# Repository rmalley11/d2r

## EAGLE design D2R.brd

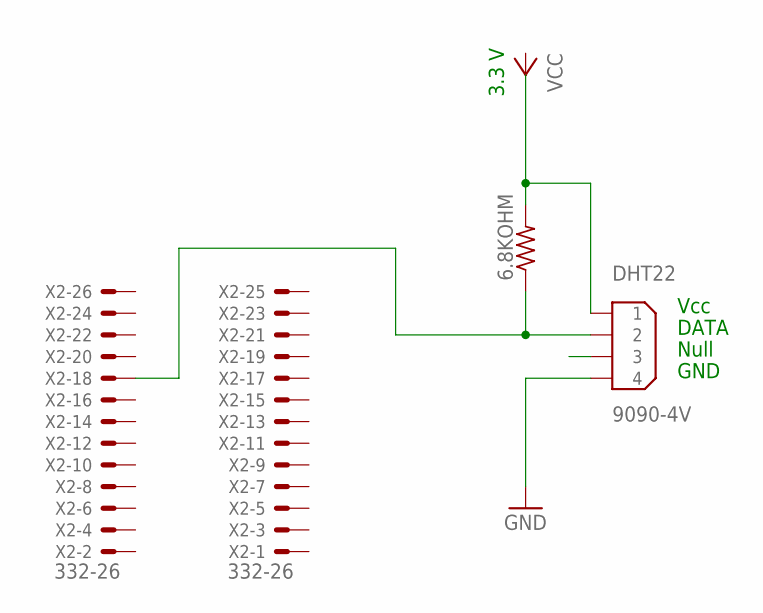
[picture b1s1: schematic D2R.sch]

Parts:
6.8KOHM: R-US_0207/10; 0207/10
DHT22: 9090-4V
X2: 332-26

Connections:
GND: DHT22.4
unnamed: 6.8KOHM.2, DHT22.1
unnamed: 6.8KOHM.1, DHT22.2, X2.18

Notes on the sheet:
3.3 V
Vcc
DATA
Null
GND

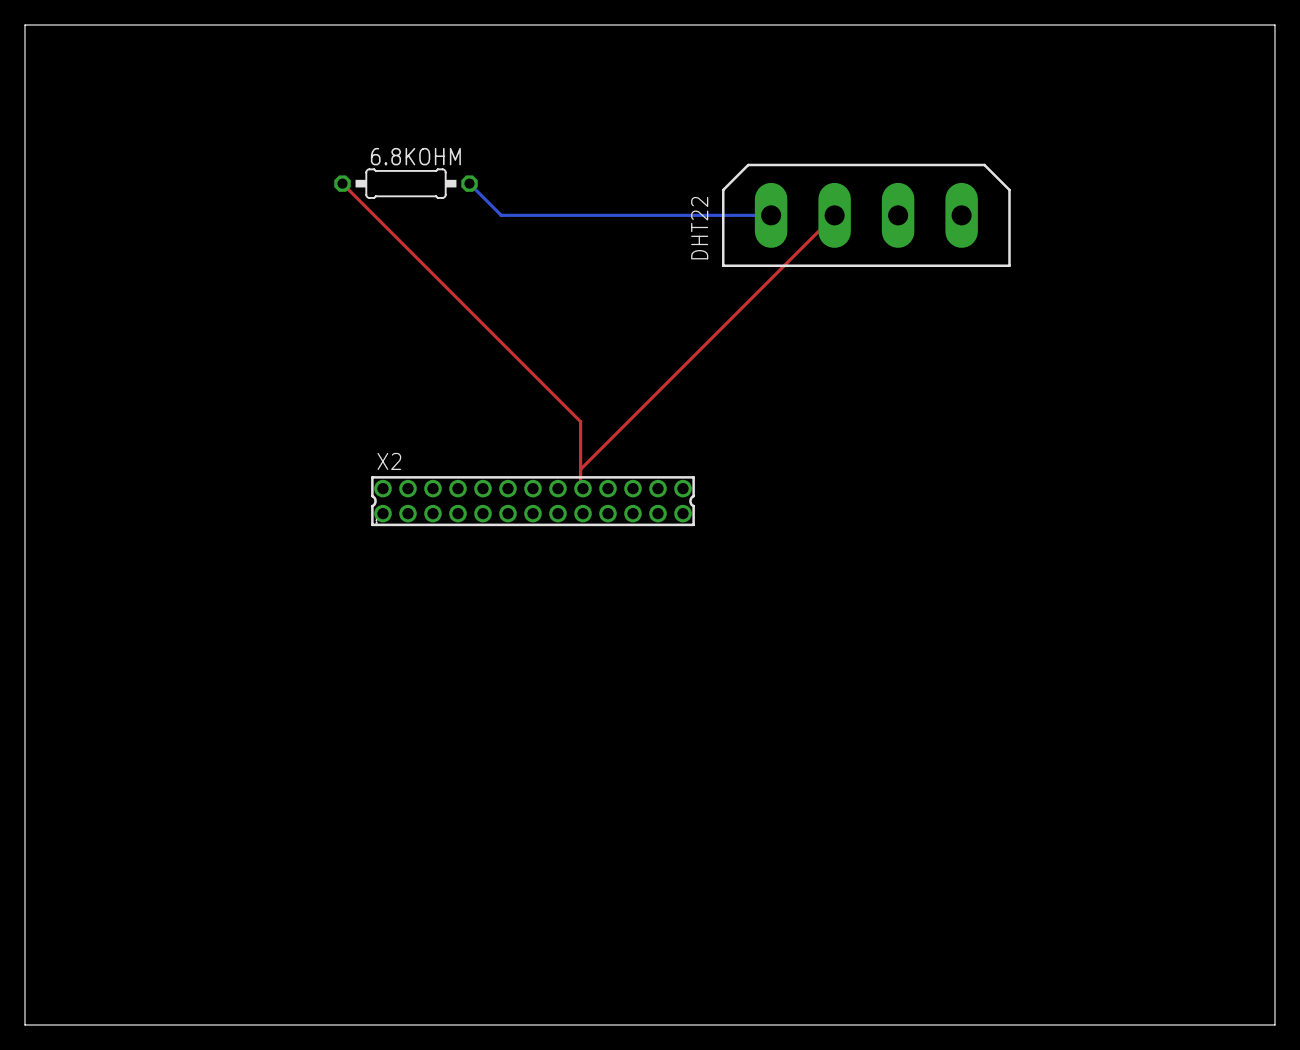
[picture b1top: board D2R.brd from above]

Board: 2 copper layers, 100.0 x 80.0 mm, 3 parts (0 on the bottom side), 2 nets.

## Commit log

2014-03-03 Quick Update
2014-03-03 Eagle Cad Files
2014-03-05 Project State
